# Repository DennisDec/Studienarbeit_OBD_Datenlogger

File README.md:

# Studienarbeit_OBD_Datenlogger
Aufbau eines Fahrzeug-GPS-Datenloggers mit WLAN-Anbindung zu einem Datenarchivierungssystem

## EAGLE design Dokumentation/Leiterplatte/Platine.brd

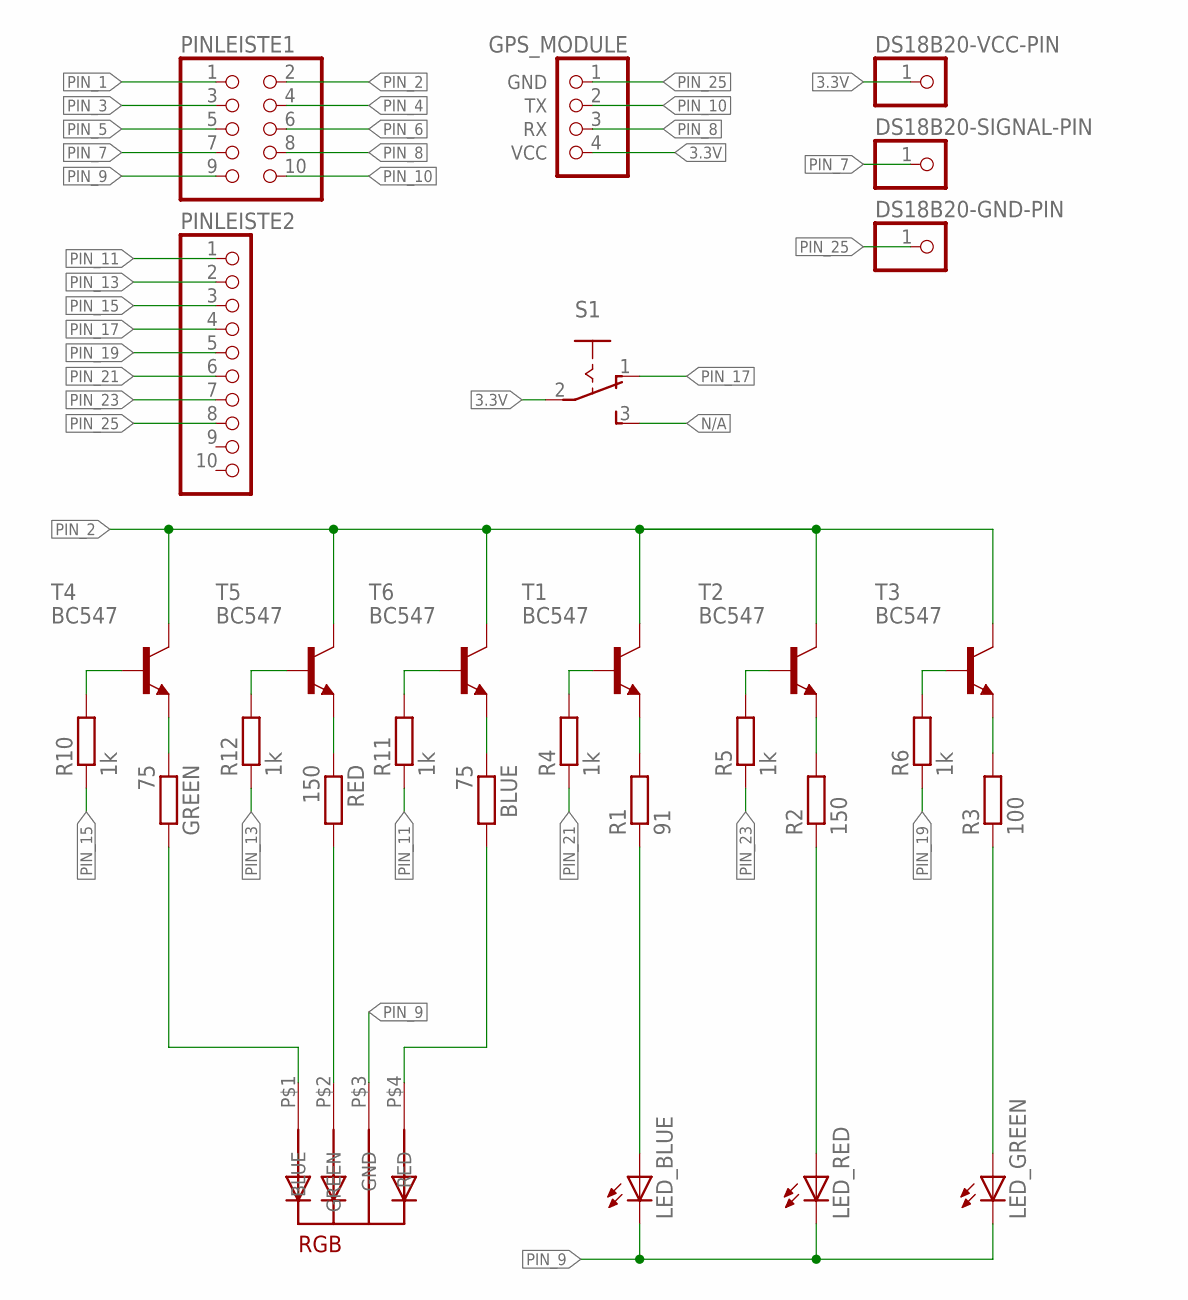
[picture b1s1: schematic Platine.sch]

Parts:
BLUE: 75; 0207/10
DS18B20-GND-PIN, DS18B20-SIGNAL-PIN, DS18B20-VCC-PIN: PINHD-1X1; 1X01
GPS_MODULE: PINHD-1X4; 1X04
GREEN: 75; 0207/10
LED_BLUE: LED5MM
LED_GREEN: LED5MM
LED_RED: LED5MM
PINLEISTE1: PINHD-2X5; 2X05
PINLEISTE2: PINHD-1X10; 1X10
R1: 91; 0207/10
R2: 150; 0207/10
R3: 100; 0207/10
R4, R5, R6, R10, R11, R12: 1k; 0207/10
RED: 150; 0207/10
RGB: 5MMRGBLED; LED5MMRGB
S1: 255SB
T1, T2, T3, T4, T5, T6: BC547; TO92

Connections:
3.3V: DS18B20-VCC-PIN.1, GPS_MODULE.4 (VCC), S1.2
unnamed: R4.2, T1.2 (B)
unnamed: R3.2, T3.1 (E)
unnamed: R2.2, T2.1 (E)
unnamed: R1.2, T1.1 (E)
unnamed: LED_BLUE.A, R1.1
unnamed: LED_RED.A, R2.1
unnamed: LED_GREEN.A, R3.1
unnamed: R5.2, T2.2 (B)
unnamed: R6.2, T3.2 (B)
unnamed: GREEN.1, T4.1 (E)
unnamed: RED.1, T5.1 (E)
unnamed: BLUE.2, RGB.P$4 (RED)
unnamed: RED.2, RGB.P$2 (GREEN)
unnamed: GREEN.2, RGB.P$1 (BLUE)
unnamed: BLUE.1, T6.1 (E)
unnamed: R10.2, T4.2 (B)
unnamed: R12.2, T5.2 (B)
unnamed: R11.2, T6.2 (B)
N/A: S1.3 (S)
PIN_1: PINLEISTE1.1
PIN_2: PINLEISTE1.2, T1.3 (C), T2.3 (C), T3.3 (C), T4.3 (C), T5.3 (C), T6.3 (C)
PIN_3: PINLEISTE1.3
PIN_4: PINLEISTE1.4
PIN_5: PINLEISTE1.5
PIN_6: PINLEISTE1.6
PIN_7: DS18B20-SIGNAL-PIN.1, PINLEISTE1.7
PIN_8: GPS_MODULE.3 (RX), PINLEISTE1.8
PIN_9: LED_BLUE.K (C), LED_GREEN.K (C), LED_RED.K (C), PINLEISTE1.9, RGB.P$3 (GND)
PIN_10: GPS_MODULE.2 (TX), PINLEISTE1.10
PIN_11: PINLEISTE2.1, R11.1
PIN_13: PINLEISTE2.2, R12.1
PIN_15: PINLEISTE2.3, R10.1
PIN_17: PINLEISTE2.4, S1.1 (O)
PIN_19: PINLEISTE2.5, R6.1
PIN_21: PINLEISTE2.6, R4.1
PIN_23: PINLEISTE2.7, R5.1
PIN_25: DS18B20-GND-PIN.1, GPS_MODULE.1 (GND), PINLEISTE2.8

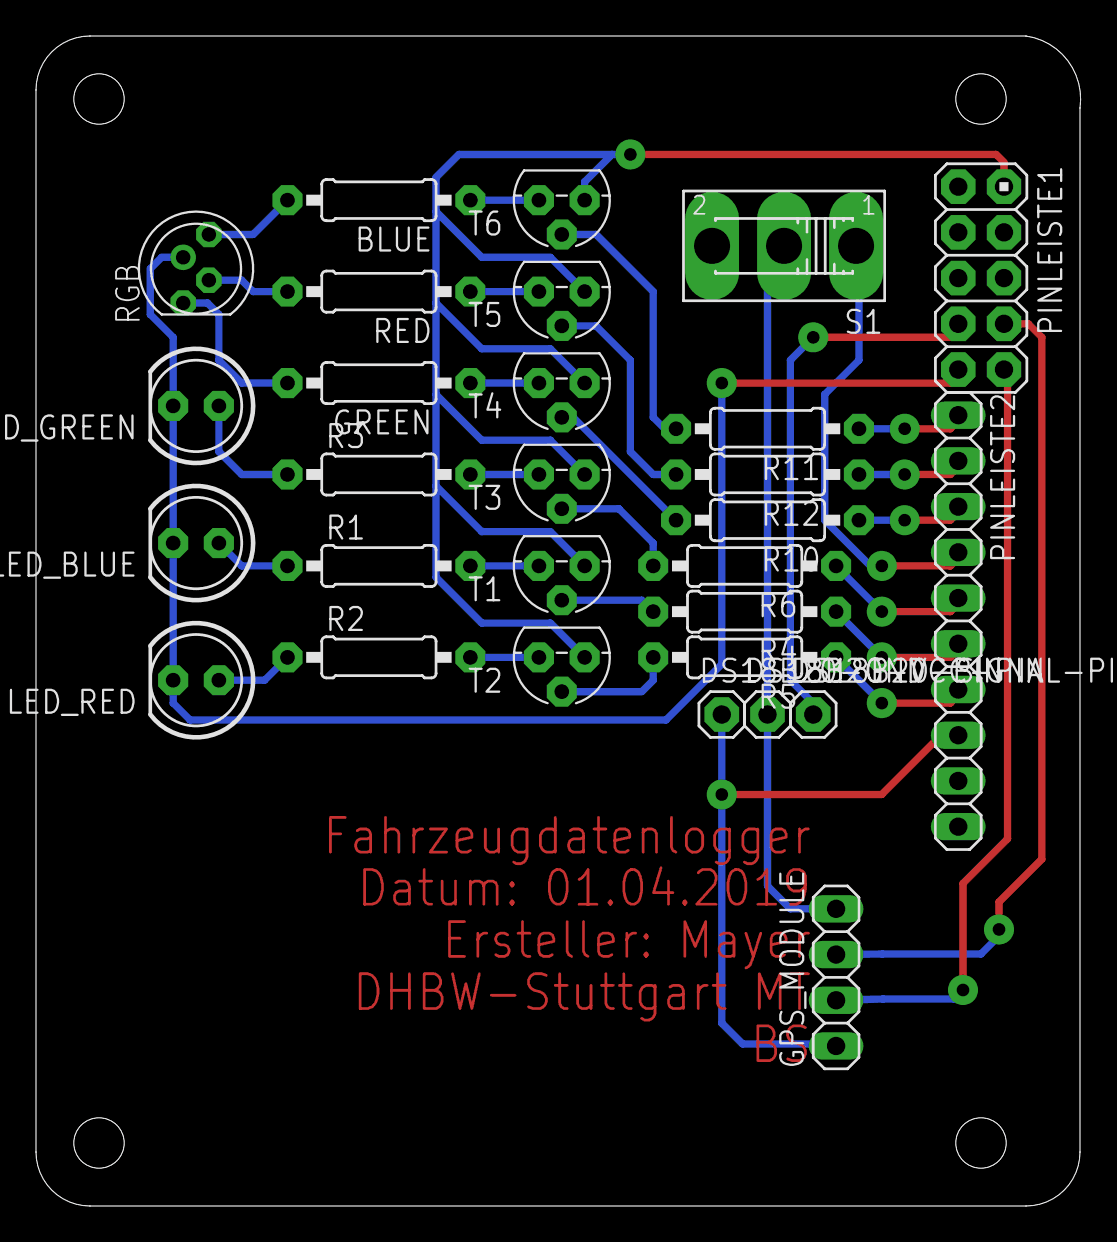
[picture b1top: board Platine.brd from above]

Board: 2 copper layers, 58.0 x 65.0 mm, 29 parts (0 on the bottom side), 32 nets.

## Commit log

2018-10-20 Add a simple express-server with MySQL-connection.
2018-10-20 Add register and login pages with register-/login-forms.
2018-10-20 Use express-validator to register new users and save them to MySQL.
2018-10-21 Set up session after successful registration, log user in and create login page.
2018-10-21 Fix the custom validator and solve the username-duplicate-error with unique usernames in MySQL and error handling in app.
2018-10-21 Add logout function to destroy session.
2018-10-21 Show user error message after failed login.
2018-10-21 Add a map to profile page with Leaflet.
2018-10-21 Import markers from json-file and print them on map.
2018-10-21 Get gps-data from MySQL and save it into json-file that leaf uses.
2018-10-21 Add lines between the markers.
2018-10-23 Save all files in seperate folder for the web-application.
2018-10-23 Added LogFile.py
2018-10-23 Added Skript for Raspbery: OBD.py
2018-10-23 Added Test.py to test LogFile.py
2018-10-23 real OBD-data csv-File
2018-10-23 Added .gitignore
2018-10-23 auto generated TestFile.csv from Test.py
2018-10-24 changed detection of Ignition-On
2018-10-24 Added some Files to .gitignore
2018-10-24 Added File to .gitignore
2018-10-24 Some changes
2018-10-25 Changes for new measurements
2018-10-25 Bug Fixes
2018-10-25 Measurement Files
2018-10-25 removed Unittest from .gitignore
2018-10-25 .gitignore changes
2018-10-25 Added Unittest for LogFile.py
2018-10-25 Some code Changes
2018-10-25 Add sidebar to web-application.
2018-10-25 Beautify the webpages.
2018-10-26 Fix dropdown navigation.
2018-10-26 Extend LogFile.py loadFromFile-method
2018-10-26 New Testcases in LogFile_test.py
2018-10-26 Added some test cases
2018-10-26 Changed Unittest
2018-10-29 Fix scroll to general data.
2018-10-29 new class OBDSignal.py to define new signals descentralized
2018-10-29 new class to store signals
2018-10-29 some changes in architecture
2018-10-29 new .gitignore
2018-10-29 new Unittests for new architecture
2018-10-30 Changed data storage in csv
2018-10-30 added unittest with "None" data
2018-11-02 no quotationmarks anymore
2018-11-02 added containsSignal() method
2018-11-02 added __eq__ method
2018-11-02 some new unittests
2018-11-02 bug fix getRelTime()
2018-11-02 no quoting anymore
2018-11-02 import changes
2018-11-02 new methods
2018-11-02 test
2018-11-02 few changes
2018-11-02 New folder for raspberry scripts.
2018-11-02 Add MySQL-Connector and Test-Wifi scripts.
2018-11-02 Add db-connector-class.
2018-11-03 Add usv-module-script.
2018-11-03 When Pi is connected to WiFi: Transmit data to MySQL
2018-11-03 Add scripts for UPS-module.
2018-11-04 Make website smartphone-compatible.
2018-11-04 Add SQL-script for database.
2018-11-04 Add a chart to the website.
2018-11-05 changes to get unittests running correctly
2018-11-05 a few changes
2018-11-05 new measurement files
2018-11-08 Change design of website.
2018-11-18 Fix dotenv-error of web-application.
2018-11-18 Fix problem: App used wrong path when started in bin directory.
2018-11-21 measurement values are now rounded to the second position after comma
2018-11-21 new signals for GPS and Time
2018-11-21 added default env
2018-11-21 beautify code
2018-11-21 added StringBuilder class
2018-11-21 Handle Signals with different sampleRate
2018-11-21 final changes from live share
2018-11-26 new script architecture
2018-11-26 Code commentation
2018-11-27 Update SQL-config-file.
2018-11-27 Raspberry server-service-script.
2018-11-27 Few changes.
2018-12-09 GPS datalogging is added
2018-12-09 better accuracy for GPS signal
2018-12-21 Send confirmation-mail.
2018-12-21 Use jsonwebtoken to generate token for confirmation-link.
2018-12-22 Only GPS-Mode has been implemented.
2018-12-22 Created seperate method for Only-GPS-Mode.
2018-12-22 Log error message of login failure.
2018-12-22 Output error messages at login failure to user.
2018-12-22 Update error messages.
2018-12-22 Resend confirmation mail after login failure.
2018-12-24 Add possibility to reset password.
2018-12-25 Get ip address.
2018-12-25 Change confirmation link.
2018-12-26 If the ip-address has changed, send mail to developer.
2019-01-05 Fix issue #7.
2019-01-05 Use plot.ly to plot the graph.
2019-02-07 current version on raspberry pi
2019-02-07 Update data transfer from backend to frontend.
2019-02-07 close #5 and data transmission process is changed
2019-02-07 Load data from MySQL to send it to frontend.
2019-02-07 call new upload function
2019-02-07 bugfix
2019-02-07 bugfix 2
2019-02-07 change sql query
2019-02-07 ToDo: Get data from file.
2019-02-08 added transferToJson method and Path-field in env
2019-02-08 Update index.js.
2019-02-08 Let transferToJson function return path of file and fix bugs.
2019-02-08 Fix transferToJson.
2019-02-08 Fix bugs at getting data from JSON file.
2019-02-08 Send a request to /getOBD with credentials included.
2019-02-09 exeption handling in transmitToServer
2019-02-09 bugfix in sshpass
2019-02-09 bugfixes
2019-02-09 save ip address
2019-02-09 bugfix2
2019-02-09 bugfix copyFileToServer
2019-02-09 change of trasferToJson-method
2019-02-09 Add dropdown menu to choose from all driving cycles.
2019-02-09 new files
2019-02-09 Add RPM-Trace.
2019-02-09 Remove old map markers.
2019-02-09 Change opacity of marker icons.
2019-02-15 Add buttons to select all trips that user wants to view.
2019-02-15 Add datepicker.
2019-02-16 Get all trips of a certain date.
2019-02-16 Bug fix of last commit #219b383e5a8fcec686339d09c3eecac5c3fadc5e.
2019-02-16 Show all trip-charts.
2019-02-16 Add map with all markers of all trips.
2019-02-17 change of frontend date format to dd.mm.yyyy
2019-02-17 Bugfix.
2019-02-17 Change style of dashboard.
2019-02-18 Configure bootstrap modal.
2019-02-18 added custom markers to map
2019-02-18 Fit first map to bounds.
2019-02-18 new dot.png
2019-02-18 Multiple axis and color changes
2019-02-18 remove chart grid
2019-02-18 Few changes in frontend.
2019-02-23 change time format to relative uptime and log gpsTime
2019-02-23 get rel time since programm started
2019-02-25 Get correct local IP.
2019-02-27 added new class for utility methods
2019-02-27 added several new methods like energy and fuel consumption
2019-02-28 Add temperature sensor funcionality
2019-02-28 Add map with waiting points.
2019-03-04 Add sample rate concept for GPS and Temperature data
2019-03-10 Update package.json.
2019-03-10 Update server-config.
2019-03-12 Bugfix: internal temperature measurement
2019-03-12 bugfix for RaspberryPi in loadFromFile
2019-03-12 Use VIN to select trips.
2019-03-12 hotfix in copyToServer
2019-03-12 hotfix2
2019-03-12 Stop refreshing page after pushing enter.
2019-03-12 Enable sundays in datepicker.
2019-03-13 clean repository
2019-03-14 Compare hashed VIN.
2019-03-14 Bug fix.
2019-03-14 VIN signal was added to Signals
2019-03-14 vin datalogging was added
2019-03-14 new absolute path to work with
2019-03-14 added getHashedVIN and parseVIN methods
2019-03-14 Modification of copyFileToServer with SQL query.
2019-03-14 Changed time to relTime.
2019-03-14 EndLat and EndLong have been added.
2019-03-15 New class to handle gps logging in thread.
2019-03-17 Setup of gps-logging in a seperate thread.
2019-03-17 Bugfix in VIN hash method.
2019-03-17 Decode hashed VIN to utf-8.
2019-03-17 Sort the list of returned filenames.
2019-03-17 Directory to store old logfiles
2019-03-17 Move csv file to Files/OLD after upload to Server.
2019-03-17 Change file ending of OnlyGpsMode
2019-03-17 Bugfix in LogFile.py
2019-03-19 Changed order of methods.
2019-03-19 Update gitignore.
2019-03-19 Upload of requirements.txt for python project.
2019-03-19 Remove import numpy from Signals.py.
2019-03-22 Service file to start OBD.py at startup of RasPi.
2019-03-22 Check if altitude is available bevore use it.
2019-03-28 Change opacity of waiting markers.
2019-03-28 Add VIN input at start of pageload.
2019-03-29 Asynchronous OBD logging and temperature logging.
2019-03-29 Decrease sample rate of temperature.
2019-03-29 Change return intend of getGpsData().
2019-04-01 Change of CopyToServer method.
2019-04-08 Insert cars into db and get them on web-app.
2019-04-09 Service to automatically connect OBD-II adapter.
2019-04-10 Choose car with range that fits to average trip.
2019-04-17 Added Logfile to usv-modul.py.
2019-04-18 Add chosen car information.
2019-04-23 Adjusted copyFileToServer und usv-script.
2019-04-23 Adjusted piupsmon.config.
2019-04-30 Choose the correct car.
2019-05-04 Insert cars into cars table.
2019-05-04 Update Raspberry Pi changes to repo.
2019-05-04 Created unittests for LogFile.
2019-05-04 Update Util class.
2019-05-04 Correct the calculation of the energy consumption.
2019-05-05 Add comments to the code.
2019-05-05 Change of efficiency values.
2019-05-05 Changed Table description.
2019-05-05 Changed ending of testfiles.
2019-05-05 Unittest changes.
2019-05-05 Change unittests.
2019-05-06 Give message when there is no trip yet.
2019-05-06 Use last GPS-Signal for time calculation.
2019-08-26 add directory Dokumentation
2019-08-26 Stückliste Gesamtsystem
2019-08-26 create directory Datenblätter
2019-08-26 add directory
2019-08-26 add data sheet files
2019-08-26 add GPS_Modul.txt
2019-08-26 create directory Platine
2019-08-26 add eagle files for PCB layout
2019-10-30 Bump morgan from 1.7.0 to 1.9.1 in /web-application
    Bumps [morgan](https://github.com/expressjs/morgan) from 1.7.0 to 1.9.1.
    - [Release notes](https://github.com/expressjs/morgan/releases)
    - [Changelog](https://github.com/expressjs/morgan/blob/master/HISTORY.md)
    - [Commits](https://github.com/expressjs/morgan/compare/1.7.0...1.9.1)
2020-08-20 Bump bcrypt from 3.0.8 to 5.0.0 in /web-application
    Bumps [bcrypt](https://github.com/kelektiv/node.bcrypt.js) from 3.0.8 to 5.0.0.
    - [Release notes](https://github.com/kelektiv/node.bcrypt.js/releases)
    - [Changelog](https://github.com/kelektiv/node.bcrypt.js/blob/master/CHANGELOG.md)
    - [Commits](https://github.com/kelektiv/node.bcrypt.js/compare/v3.0.8...v5.0.0)
2020-09-04 Bump node-sass from 3.13.1 to 4.14.1 in /web-application
    Bumps [node-sass](https://github.com/sass/node-sass) from 3.13.1 to 4.14.1.
    - [Release notes](https://github.com/sass/node-sass/releases)
    - [Changelog](https://github.com/sass/node-sass/blob/master/CHANGELOG.md)
    - [Commits](https://github.com/sass/node-sass/compare/v3.13.1...v4.14.1)
